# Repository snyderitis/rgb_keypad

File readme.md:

# 20keyrgb

A short description of the keyboard/project

Keyboard Maintainer: [Snyderitis](https://github.com/snyderitis)  
Hardware Supported: The kicad files for the PCB are in the "RGB keyboard" folder. 
Hardware Availability: I used WS2812B leds with 0.1uF SMD capacitors and a teensy. In the future it would be wiser to use an Arduino Pro mini as they're essentially the same and have the same pin layout.

Make example for this keyboard (after setting up your build environment):

    make 20keyrgb:default

See [build environment setup](https://docs.qmk.fm/build_environment_setup.html) then the [make instructions](https://docs.qmk.fm/make_instructions.html) for more information.

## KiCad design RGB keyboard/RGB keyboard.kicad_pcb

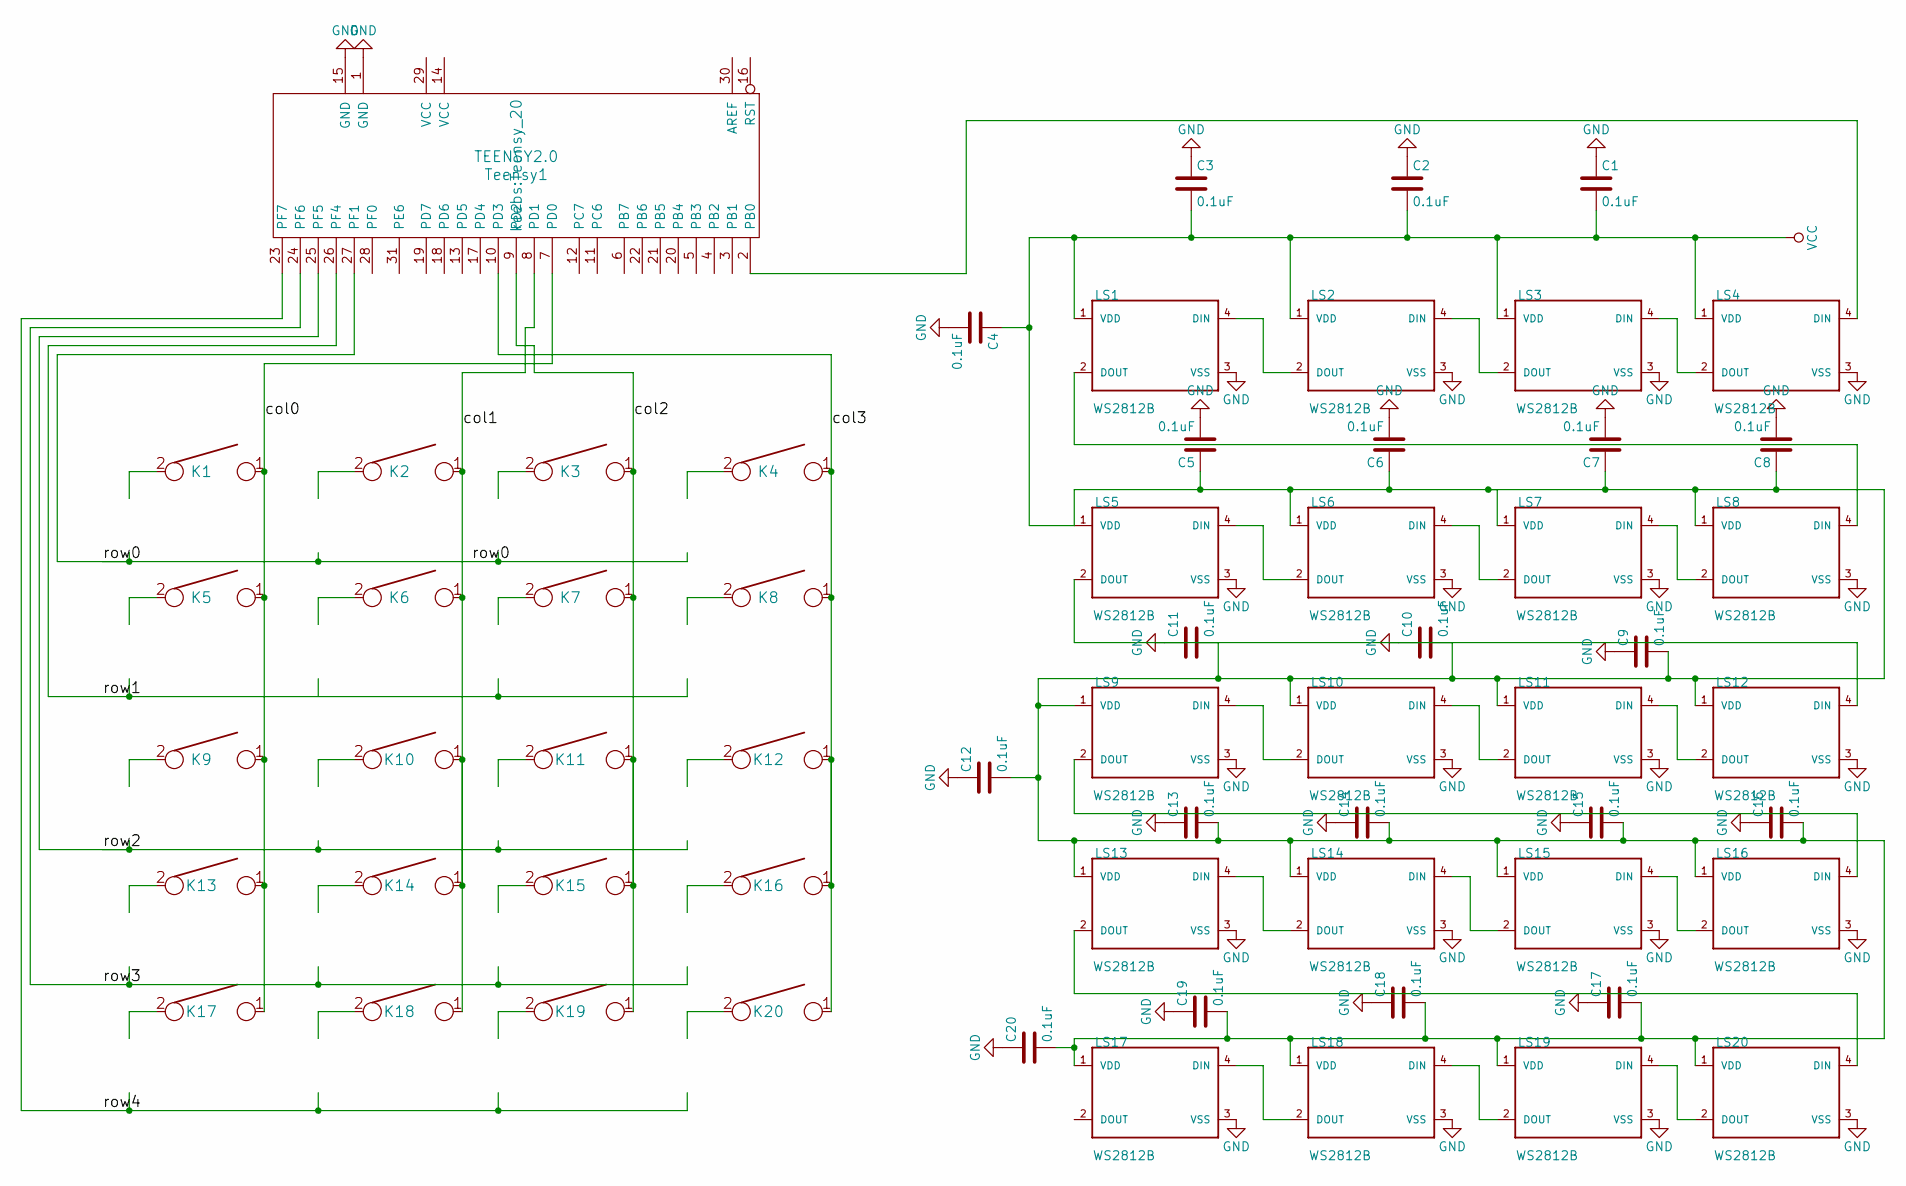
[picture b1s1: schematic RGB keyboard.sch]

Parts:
C1, C2, C3, C4, C5, C6, C7, C8, C9, C10, C11, C12, C13, C14, C15, C16, C17, C18, C19, C20: 0.1uF; C_0805_HandSoldering
K1, K2, K3, K4, K5, K6, K7, K8, K9, K10, K11, K12, K13, K14, K15, K16, K17, K18, K19, K20: KEYSW; Mx_Alps_100
LS1, LS2, LS3, LS4, LS5, LS6, LS7, LS8, LS9, LS10, LS11, LS12, LS13, LS14, LS15, LS16, LS17, LS18, LS19, LS20: WS2812B
Teensy1: TEENSY2.0; Teensy_20

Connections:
/col0: K1.1, K5.1, K9.1, K13.1, K17.1, Teensy1.7 (PD0)
/col1: K2.1, K6.1, K10.1, K14.1, K18.1, Teensy1.8 (PD1)
/col2: K3.1, K7.1, K11.1, K15.1, K19.1, Teensy1.9 (PD2)
/col3: K4.1, K8.1, K12.1, K16.1, K20.1, Teensy1.10 (PD3)
/row0: Teensy1.27 (PF1)
/row1: Teensy1.26 (PF4)
/row2: Teensy1.25 (PF5)
/row3: Teensy1.24 (PF6)
/row4: Teensy1.23 (PF7)
unnamed: LS1.2 (DOUT), LS8.4 (DIN)
unnamed: LS1.4 (DIN), LS2.2 (DOUT)
unnamed: LS2.4 (DIN), LS3.2 (DOUT)
unnamed: LS3.4 (DIN), LS4.2 (DOUT)
unnamed: LS4.4 (DIN), Teensy1.2 (PB0)
unnamed: LS5.4 (DIN), LS6.2 (DOUT)
unnamed: LS6.4 (DIN), LS7.2 (DOUT)
unnamed: LS7.4 (DIN), LS8.2 (DOUT)
unnamed: LS9.4 (DIN), LS10.2 (DOUT)
unnamed: LS10.4 (DIN), LS11.2 (DOUT)
unnamed: LS11.4 (DIN), LS12.2 (DOUT)
unnamed: LS13.2 (DOUT), LS20.4 (DIN)
unnamed: LS13.4 (DIN), LS14.2 (DOUT)
unnamed: LS14.4 (DIN), LS15.2 (DOUT)
unnamed: LS15.4 (DIN), LS16.2 (DOUT)
unnamed: LS9.2 (DOUT), LS16.4 (DIN)
unnamed: LS17.4 (DIN), LS18.2 (DOUT)
unnamed: LS18.4 (DIN), LS19.2 (DOUT)
unnamed: LS19.4 (DIN), LS20.2 (DOUT)
VCC: C1.2, C2.2, C3.2, C4.1, C5.1, C6.1, C7.1, C8.1, C9.2, C10.2, C11.2, C12.2, C13.2, C14.2, C15.2, C16.2, C17.2, C18.2, C19.2, C20.2, LS1.1 (VDD), LS2.1 (VDD), LS3.1 (VDD), LS4.1 (VDD), LS5.1 (VDD), LS6.1 (VDD), LS7.1 (VDD), LS8.1 (VDD), LS9.1 (VDD), LS10.1 (VDD), LS11.1 (VDD), LS12.1 (VDD), LS13.1 (VDD), LS14.1 (VDD), LS15.1 (VDD), LS16.1 (VDD), LS17.1 (VDD), LS18.1 (VDD), LS19.1 (VDD), LS20.1 (VDD)

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
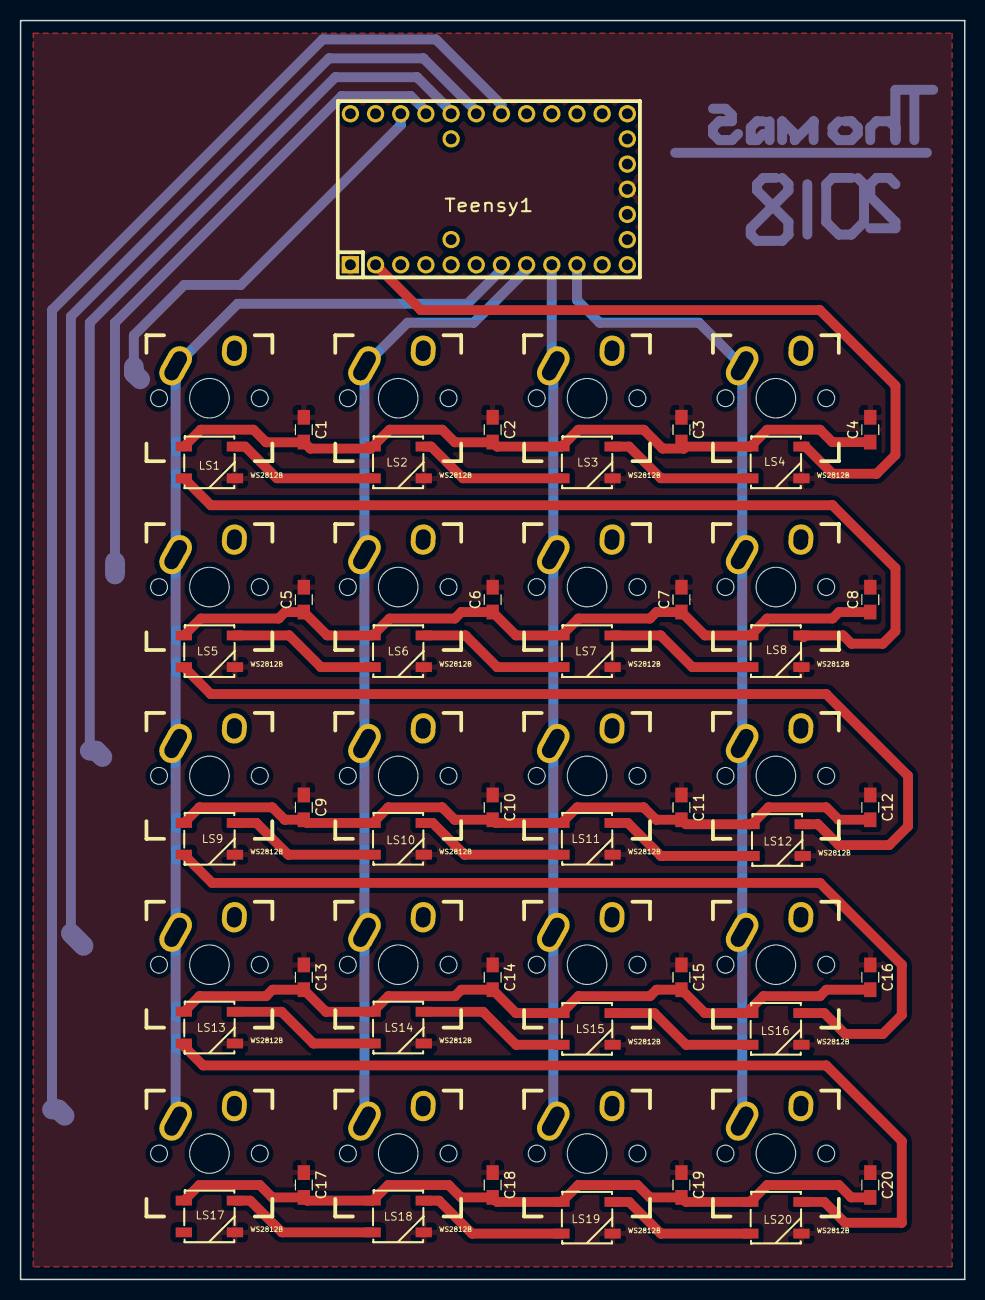
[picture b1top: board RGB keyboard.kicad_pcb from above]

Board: 2 copper layers, 95.2 x 127.0 mm, 61 parts (0 on the bottom side), 26 nets.

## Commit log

2018-03-23 first
2018-03-23 added kicad files
2018-03-23 New RGB animations
2018-03-23 Commented switch cases for rgbs
2018-03-23 commented for direction in rainbow swirl
